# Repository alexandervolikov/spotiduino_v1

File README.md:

Sportiduino_v1

v. 1.6.0.

Данная версия используется мной для моих станций, имеется некоторая специфика работы а также элементы, несовместимые с основной версией.

Общеподдерживаямая версия находится тут: https://github.com/sportiduino/sportiduino

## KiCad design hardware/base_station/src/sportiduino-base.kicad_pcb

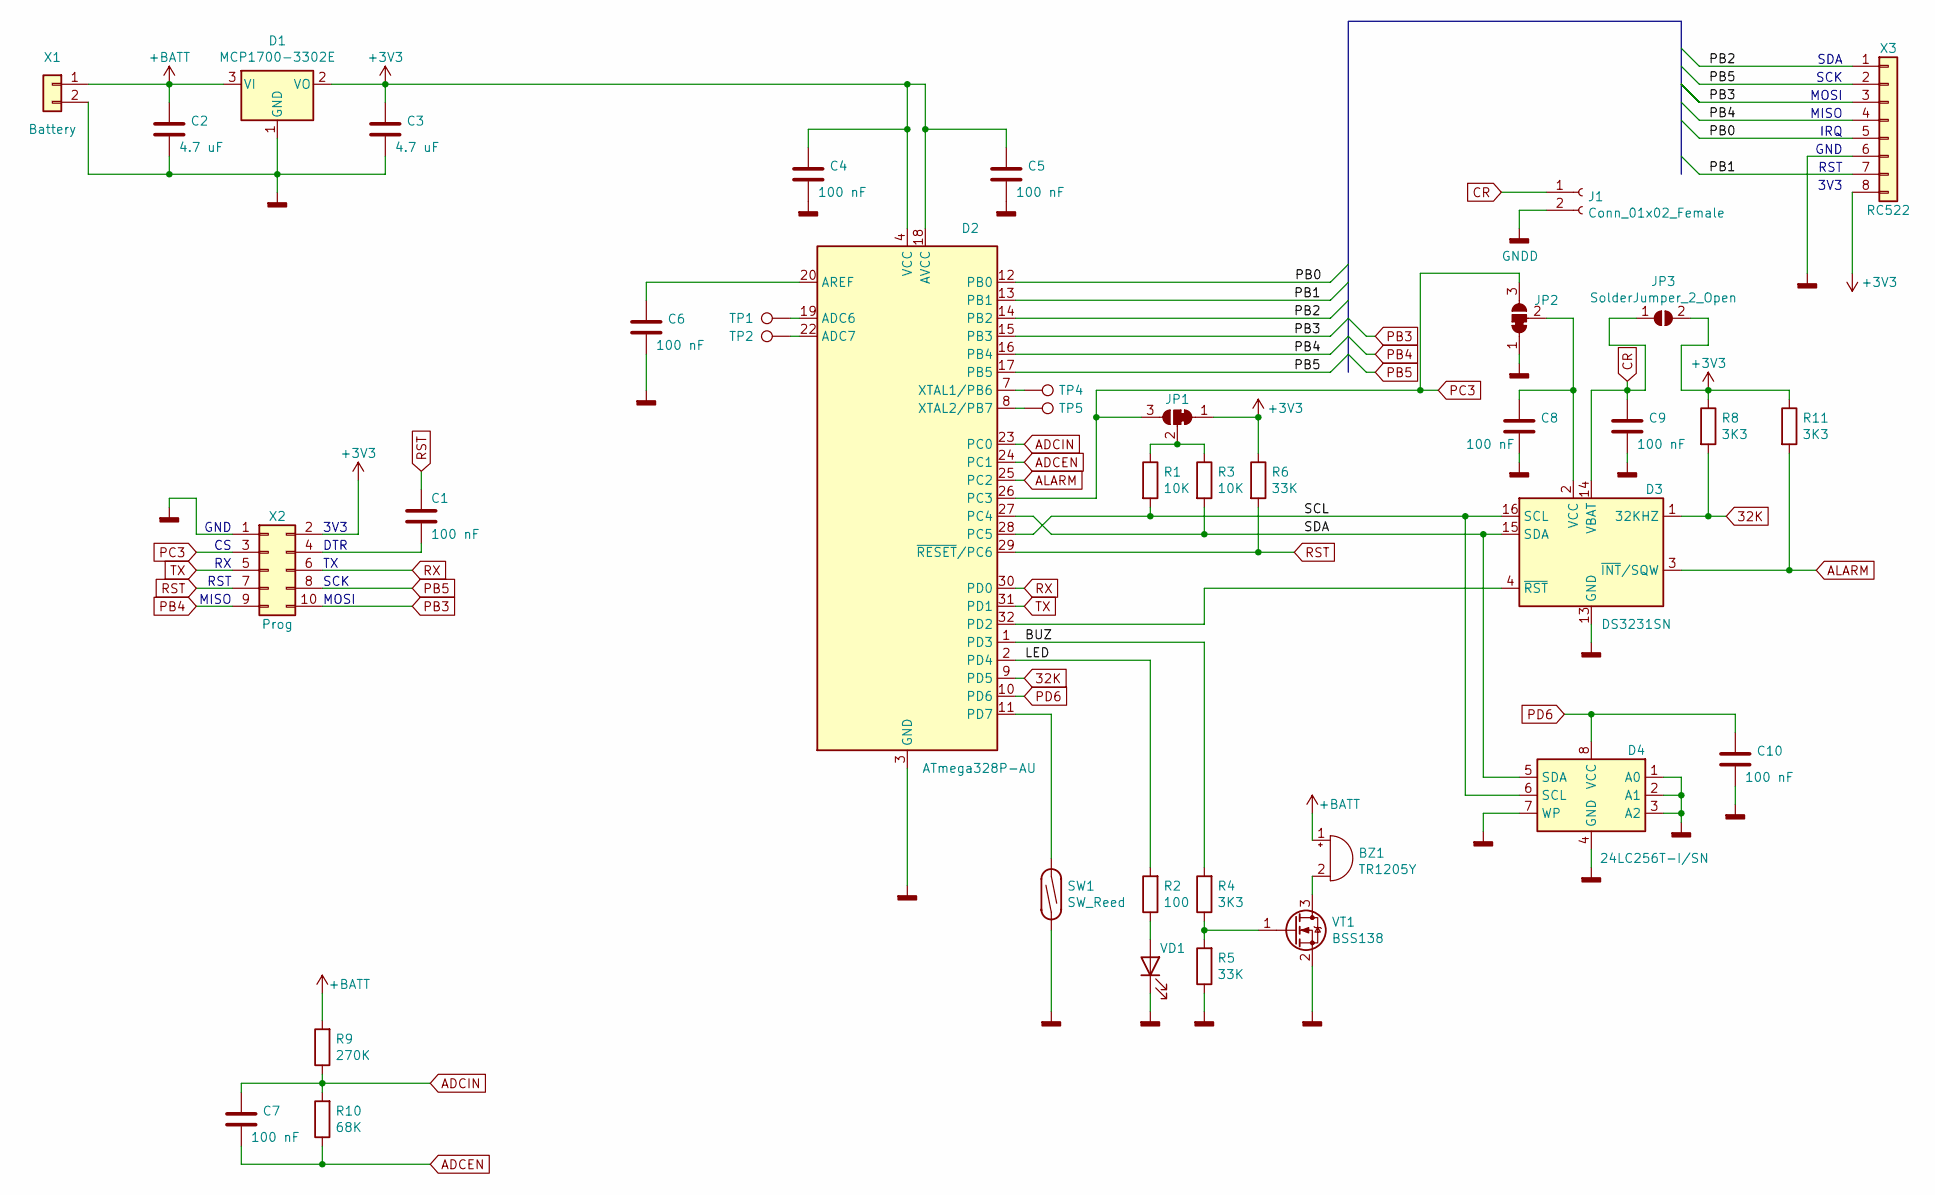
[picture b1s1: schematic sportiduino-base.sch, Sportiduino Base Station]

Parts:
BZ1: TR1205Y; MagneticBuzzer_ProSignal_ABT-410-RC
C1, C4, C5, C6, C7, C8, C9, C10: 100 nF; C_0805_2012Metric_Pad1.15x1.40mm_HandSolder
C2, C3: 4.7 uF; C_0805_2012Metric_Pad1.15x1.40mm_HandSolder
D1: MCP1700-3302E; SOT-23_Handsoldering
D2: ATmega328P-AU; TQFP-32_7x7mm_P0.8mm
D3: DS3231SN; SOIC-16W_7.5x10.3mm_P1.27mm
D4: 24LC256T-I/SN; SOIC-8_3.9x4.9mm_P1.27mm
J1: Conn_01x02_Female; PinHeader_1x02_P2.54mm_Vertical
JP1, JP2: SolderJumper_3_Bridged12; SolderJumper-3_P1.3mm_Open_RoundedPad1.0x1.5mm_NumberLabels
JP3: SolderJumper_2_Open; SolderJumper-2_P1.3mm_Open_RoundedPad1.0x1.5mm
R1, R3: 10K; R_0805_2012Metric_Pad1.15x1.40mm_HandSolder
R2: 100; R_0805_2012Metric_Pad1.15x1.40mm_HandSolder
R4, R8, R11: 3K3; R_0805_2012Metric_Pad1.15x1.40mm_HandSolder
R5, R6: 33K; R_0805_2012Metric_Pad1.15x1.40mm_HandSolder
R9: 270K; R_0805_2012Metric_Pad1.15x1.40mm_HandSolder
R10: 68K; R_0805_2012Metric_Pad1.15x1.40mm_HandSolder
SW1: SW_Reed; SW_reed
TP1, TP2, TP4, TP5: TestPoint; TestPoint_THTPad_D1.5mm_Drill0.7mm
VD1: 3mm; LED_D3.0mm
VT1: BSS138; SOT-23_Handsoldering
X1: Battery; PinHeader_1x02_P2.54mm_Vertical
X2: Prog; IDC-Header_2x05_P2.54mm_Vertical
X3: RC522; PinHeader_1x08_P2.54mm_Vertical

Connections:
32K: D2.9 (PD5), D3.1 (32KHZ), R8.2
+3V3: C3.1, C4.1, C5.1, D1.2 (VO), D2.4 (VCC), D2.6 (VCC), D2.18 (AVCC), JP1.1 (A), JP3.2 (B), R6.1, R8.1, R11.1, X2.2, X3.8
+BATT: BZ1.1 (-), C2.1, D1.3 (VI), R9.2, X1.1
/BUZ: D2.1 (PD3), R4.2
/LED: D2.2 (PD4), R2.2
/PB0: D2.12 (PB0), X3.5
/PB1: D2.13 (PB1), X3.7
/PB2: D2.14 (PB2), X3.1
/SCL: D2.28 (PC5), D3.16 (SCL), D4.6 (SCL), R1.2
/SDA: D2.27 (PC4), D3.15 (SDA), D4.5 (SDA), R3.2
ADCEN: C7.2, D2.24 (PC1), R10.1
ADCIN: C7.1, D2.23 (PC0), R9.1, R10.2
ALARM: D2.25 (PC2), D3.3 (~INT~/SQW), R11.2
CR: C9.1, D3.14 (VBAT), J1.1, JP3.1 (A)
GNDD: C2.2, C3.2, C4.2, C5.2, C6.2, C8.2, C9.2, C10.2, D1.1 (GND), D2.3 (GND), D2.5 (GND), D2.21 (GND), D3.5 (GND), D3.6 (GND), D3.7 (GND), D3.8 (GND), D3.9 (GND), D3.10 (GND), D3.11 (GND), D3.12 (GND), D3.13 (GND), D4.1 (A0), D4.2 (A1), D4.3 (A2), D4.4 (GND), D4.7 (WP), J1.2, JP2.1 (A), R5.1, SW1.2, VD1.1 (K), VT1.2 (S), X1.2, X2.1, X3.6
unnamed: BZ1.2 (+), VT1.3 (D)
unnamed: C1.2, X2.4
unnamed: C6.1, D2.20 (AREF)
unnamed: C8.1, D3.2 (VCC), JP2.2 (C)
unnamed: D2.7 (XTAL1/PB6), TP4.1
unnamed: D2.8 (XTAL2/PB7), TP5.1
unnamed: D2.11 (PD7), SW1.1
unnamed: D2.19 (ADC6), TP1.1
unnamed: D2.22 (ADC7), TP2.1
unnamed: D2.32 (PD2), D3.4 (~RST)
unnamed: JP1.2 (C), R1.1, R3.1
unnamed: R2.1, VD1.2 (A)
unnamed: R4.1, R5.2, VT1.1 (G)
PB3: D2.15 (PB3), X2.10, X3.3
PB4: D2.16 (PB4), X2.9, X3.4
PB5: D2.17 (PB5), X2.8, X3.2
PC3: D2.26 (PC3), JP1.3 (B), JP2.3 (B), X2.3
PD6: C10.1, D2.10 (PD6), D4.8 (VCC)
RST: C1.1, D2.29 (~RESET~/PC6), R6.2, X2.7
RX: D2.30 (PD0), X2.6
TX: D2.31 (PD1), X2.5

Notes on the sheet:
RST
GND
IRQ
MISO
MOSI
SCK
SDA
3V3
DTR

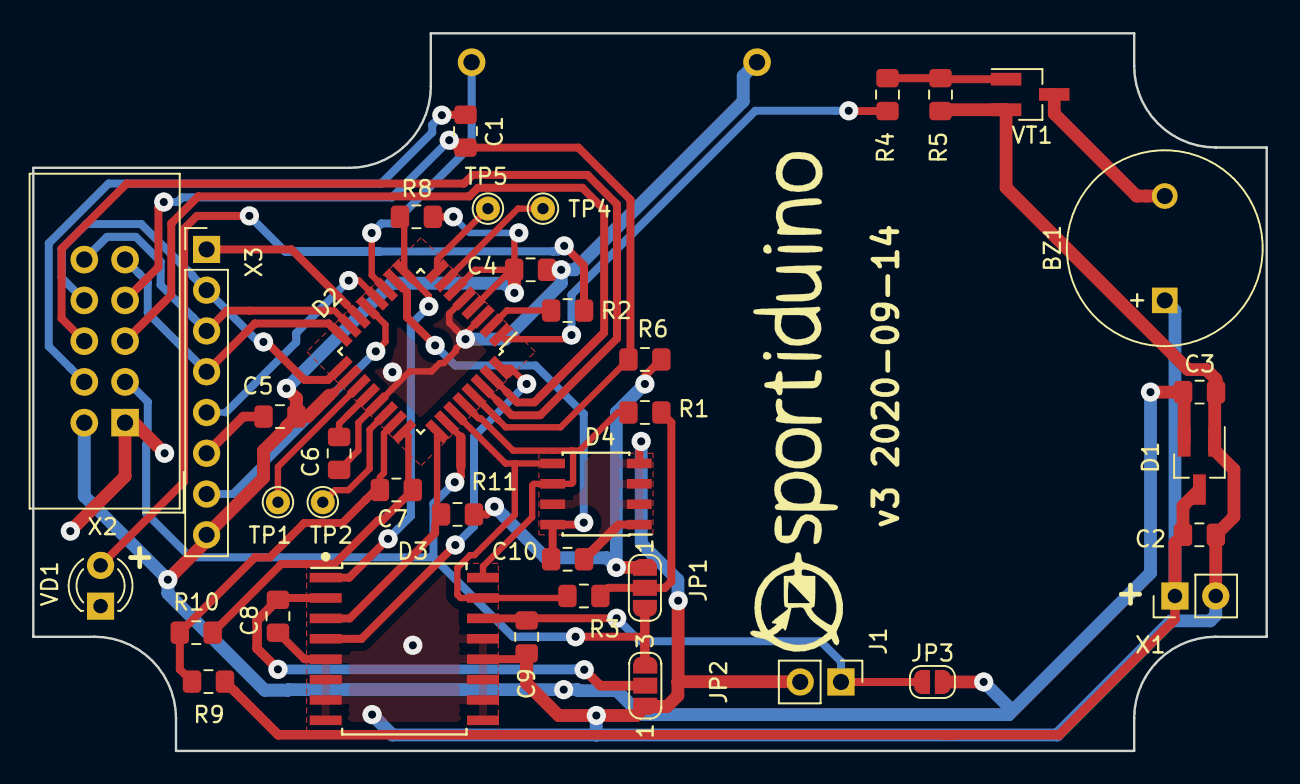
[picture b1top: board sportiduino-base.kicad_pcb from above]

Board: 2 copper layers, 76.8 x 44.7 mm, 39 parts (1 on the bottom side), 36 nets.

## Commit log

2020-10-25 v. 1.5.0
2020-10-25 add chip and version info to init
2020-10-25 add separate ntag password
2021-09-12 1.6.0
